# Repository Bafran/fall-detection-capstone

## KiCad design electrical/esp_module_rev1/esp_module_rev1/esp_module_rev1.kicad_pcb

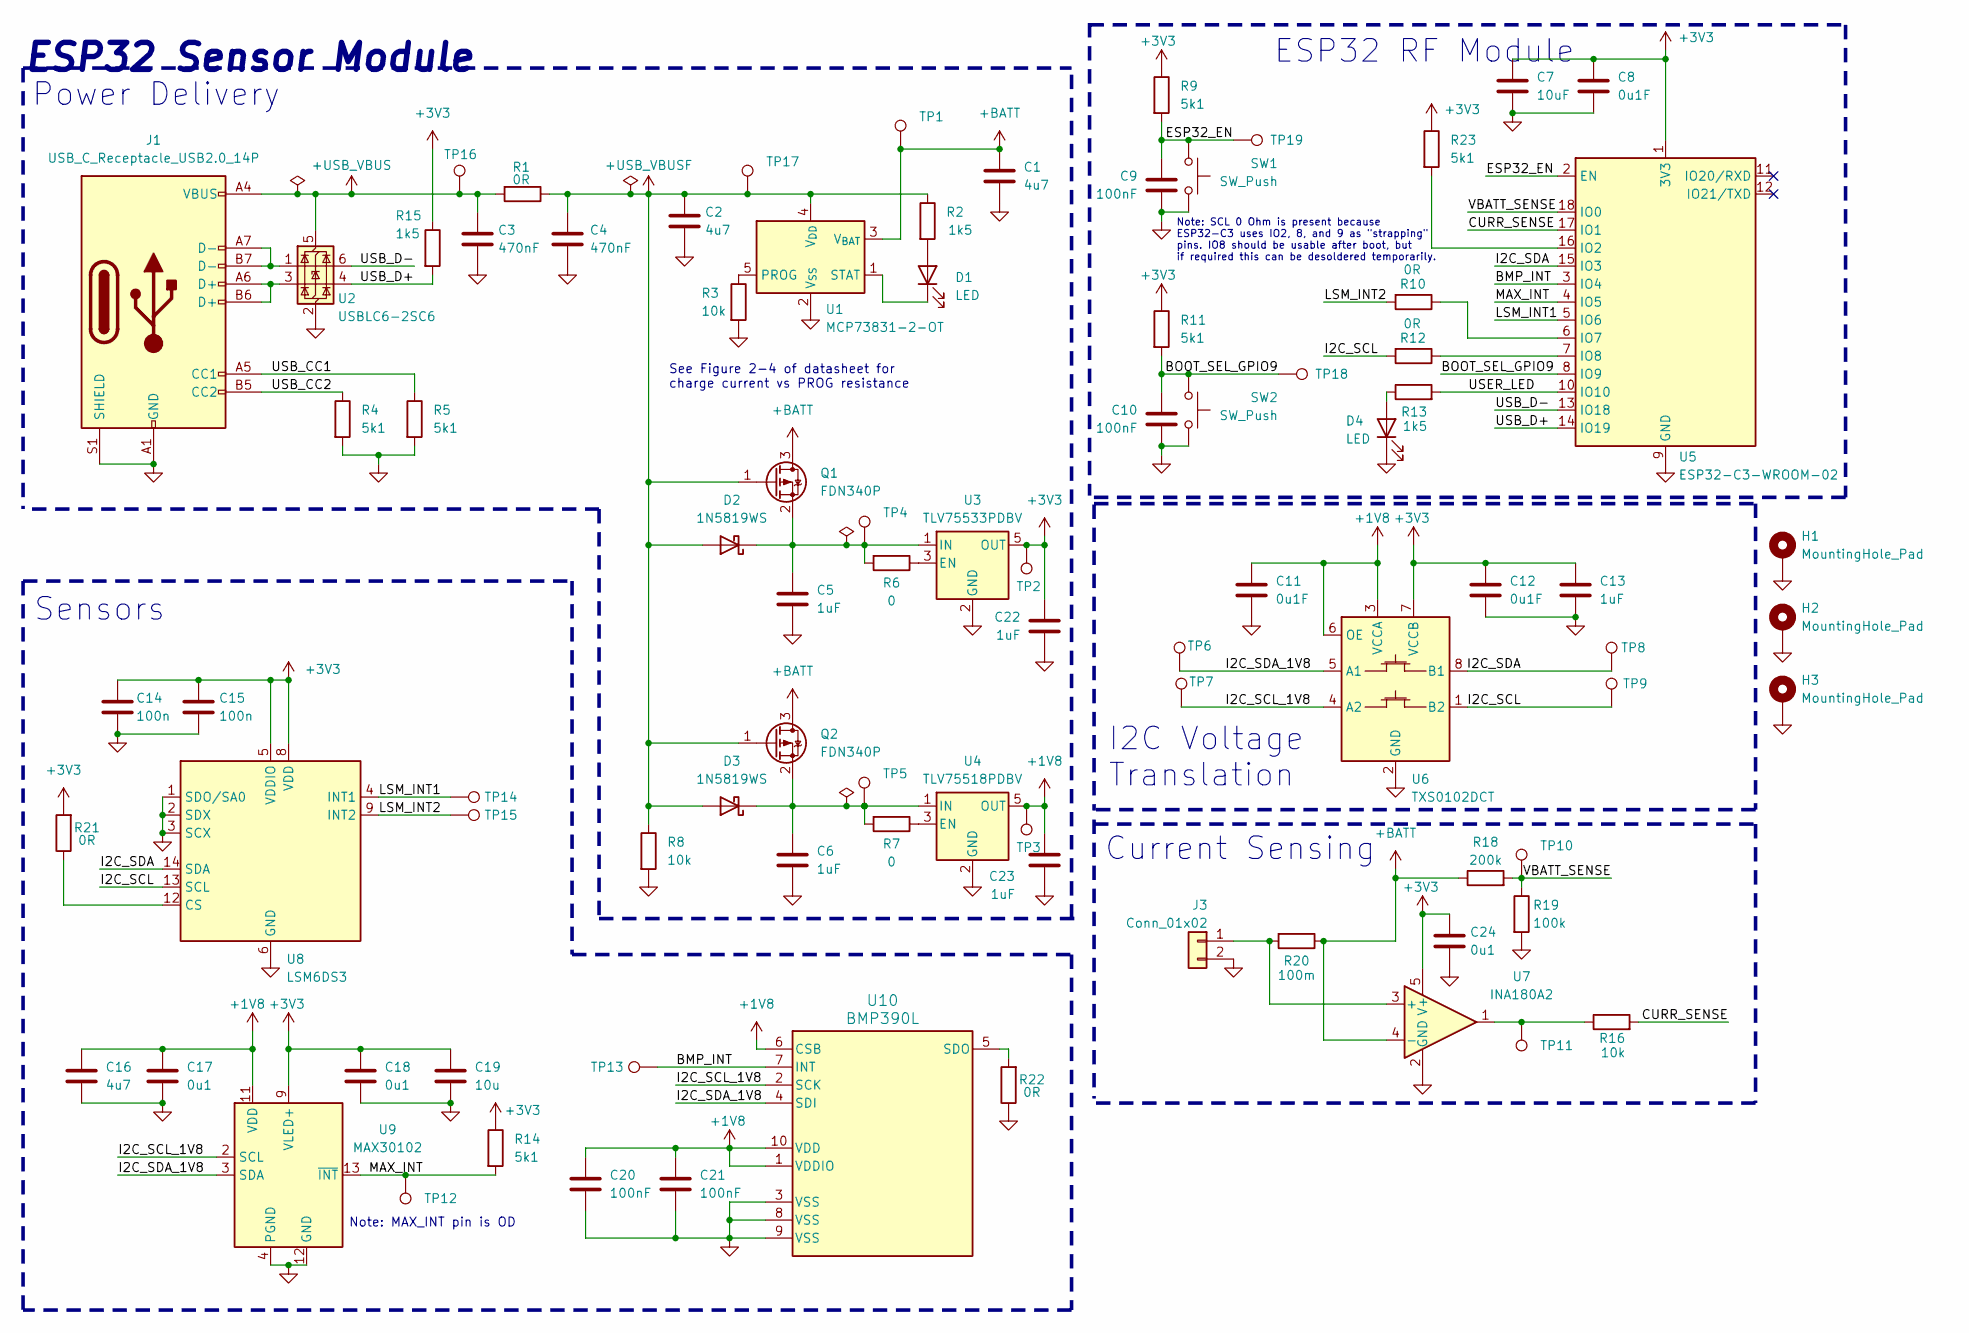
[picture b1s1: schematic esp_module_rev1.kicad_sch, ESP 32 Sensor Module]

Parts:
C1, C2, C16: 4u7; C_0603_1608Metric_Pad1.08x0.95mm_HandSolder
C3, C4: 470nF; C_0603_1608Metric_Pad1.08x0.95mm_HandSolder
C5, C6, C13, C22, C23: 1uF; C_0603_1608Metric_Pad1.08x0.95mm_HandSolder
C7: 10uF; C_0603_1608Metric_Pad1.08x0.95mm_HandSolder
C8, C11, C12: 0u1F; C_0603_1608Metric_Pad1.08x0.95mm_HandSolder
C9, C10, C20, C21: 100nF; C_0603_1608Metric_Pad1.08x0.95mm_HandSolder
C14, C15: 100n; C_0603_1608Metric_Pad1.08x0.95mm_HandSolder
C17, C18, C24: 0u1; C_0603_1608Metric_Pad1.08x0.95mm_HandSolder
C19: 10u; C_0603_1608Metric_Pad1.08x0.95mm_HandSolder
D1: LED; LED_0805_2012Metric_Pad1.15x1.40mm_HandSolder
D2, D3: 1N5819WS; D_SOD-323
D4: LED; LED_1206_3216Metric_Pad1.42x1.75mm_HandSolder
H1, H2, H3: MountingHole_Pad; MountingHole_2.2mm_M2_Pad_Via
J1: USB_C_Receptacle_USB2.0_14P; USB_C_Receptacle_GCT_USB4105-xx-A_16P_TopMnt_Horizontal
J3: Conn_01x02; JST_PH_B2B-PH-K_1x02_P2.00mm_Vertical
Q1, Q2: FDN340P; SOT-23
R1, R10, R12, R21, R22: 0R; R_0603_1608Metric_Pad0.98x0.95mm_HandSolder
R2, R13, R15: 1k5; R_0603_1608Metric_Pad0.98x0.95mm_HandSolder
R3, R8, R16: 10k; R_0603_1608Metric_Pad0.98x0.95mm_HandSolder
R4, R5, R9, R11, R14, R23: 5k1; R_0603_1608Metric_Pad0.98x0.95mm_HandSolder
R6, R7: 0; R_0603_1608Metric_Pad0.98x0.95mm_HandSolder
R18: 200k; R_0603_1608Metric_Pad0.98x0.95mm_HandSolder
R19: 100k; R_0603_1608Metric_Pad0.98x0.95mm_HandSolder
R20: 100m; R_0603_1608Metric_Pad0.98x0.95mm_HandSolder
SW1, SW2: SW_Push; SW_PUSH_6mm
TP1, TP2, TP3, TP4, TP5, TP6, TP7, TP8, TP9, TP10, TP11, TP12, TP13, TP14, TP15, TP16, TP17, TP18, TP19: TestPoint; TestPoint_THTPad_D1.5mm_Drill0.7mm
U1: MCP73831-2-OT; SOT-23-5
U2: USBLC6-2SC6; SOT-23-6
U3: TLV75533PDBV; SOT-23-5
U4: TLV75518PDBV; SOT-23-5
U5: ESP32-C3-WROOM-02
U6: TXS0102DCT; SSOP-8_2.95x2.8mm_P0.65mm
U7: INA180A2; SOT-23-5
U8: LSM6DS3; LGA-14_3x2.5mm_P0.5mm_LayoutBorder3x4y
U9: MAX30102; Maxim_OLGA-14_3.3x5.6mm_P0.8mm
U10: BMP390L; 10LGA_2X2X0p75_BOS

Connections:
+1V8: C11.1, C16.1, C17.1, C20.1, C21.1, C23.1, TP3.1, U4.5 (OUT), U6.3 (VCCA), U6.6 (OE), U9.11 (VDD), U10.1 (VDDIO), U10.6 (CSB), U10.10 (VDD)
+3V3: C7.1, C8.1, C12.1, C13.1, C14.1, C15.1, C18.1, C19.1, C22.1, C24.1, R9.1, R11.1, R14.1, R15.1, R21.2, R23.1, TP2.1, U3.5 (OUT), U5.1 (3V3), U6.7 (VCCB), U7.5 (V+), U8.5 (VDDIO), U8.8 (VDD), U9.9 (VLED+), U9.10 (VLED+)
+BATT: C1.1, Q1.3 (D), Q2.3 (D), R18.1, R20.1, TP1.1, U1.3 (V_{BAT}), U7.4 (-)
+USB_VBUS: C3.1, J1.A4 (VBUS), J1.A9 (VBUS), J1.B4 (VBUS), J1.B9 (VBUS), R1.2, TP16.1, U2.5 (VBUS)
+USB_VBUSF: C2.1, C4.1, D2.2 (A), D3.2 (A), Q1.1 (G), Q2.1 (G), R1.1, R2.1, R8.1, TP17.1, U1.4 (V_{DD})
/BMP_INT: TP13.1, U5.3 (IO4), U10.7 (INT)
/BOOT_SEL_GPIO9: C10.1, R11.2, SW2.2, TP18.1, U5.8 (IO9)
/CURR_SENSE: R16.2, U5.17 (IO1)
/ESP32_EN: C9.1, R9.2, SW1.2, TP19.1, U5.2 (EN)
/I2C_SCL: R12.2, TP9.1, U6.1 (B2), U8.13 (SCL)
/I2C_SCL_1V8: TP7.1, U6.4 (A2), U9.2 (SCL), U10.2 (SCK)
/I2C_SDA: TP8.1, U5.15 (IO3), U6.8 (B1), U8.14 (SDA)
/I2C_SDA_1V8: TP6.1, U6.5 (A1), U9.3 (SDA), U10.4 (SDI)
/LSM_INT1: TP14.1, U5.5 (IO6), U8.4 (INT1)
/LSM_INT2: R10.2, TP15.1, U8.9 (INT2)
/MAX_INT: R14.2, TP12.1, U5.4 (IO5), U9.13 (~INT)
/USB_CC1: J1.A5 (CC1), R5.1
/USB_CC2: J1.B5 (CC2), R4.1
/USB_D+: R15.2, U2.4 (I/O2), U5.14 (IO19)
/USB_D-: U2.6 (I/O1), U5.13 (IO18)
/USER_LED: R13.2, U5.10 (IO10)
/VBATT_SENSE: R18.2, R19.1, TP10.1, U5.18 (IO0)
GND: C1.2, C2.2, C3.2, C4.2, C5.2, C6.2, C7.2, C8.2, C9.2, C10.2, C11.2, C12.2, C13.2, C14.2, C15.2, C16.2, C17.2, C18.2, C19.2, C20.2, C21.2, C22.2, C23.2, C24.2, D4.1 (K), H1.1, H2.1, H3.1, J1.A1 (GND), J1.A12 (GND), J1.B1 (GND), J1.B12 (GND), J1.S1 (SHIELD), J3.2, R3.2, R4.2, R5.2, R8.2, R19.2, R22.1, SW1.1, SW2.1, U1.2 (V_{SS}), U2.2 (GND), U3.2 (GND), U4.2 (GND), U5.9 (GND), U5.19 (GND), U6.2 (GND), U7.2 (GND), U8.1 (SDO/SA0), U8.2 (SDX), U8.3 (SCX), U8.6 (GND), U8.7 (GND), U9.4 (PGND), U9.12 (GND), U10.3 (VSS), U10.8 (VSS), U10.9 (VSS)
unnamed: D1.2 (A), R2.2
unnamed: D1.1 (K), U1.1 (STAT)
unnamed: C5.1, D2.1 (K), Q1.2 (S), R6.2, TP4.1, U3.1 (IN)
unnamed: C6.1, D3.1 (K), Q2.2 (S), R7.2, TP5.1, U4.1 (IN)
unnamed: D4.2 (A), R13.1
unnamed: J1.A6 (D+), J1.B6 (D+), U2.3 (I/O2)
unnamed: J1.A7 (D-), J1.B7 (D-), U2.1 (I/O1)
unnamed: J3.1, R20.2, U7.3 (+)
unnamed: R16.1, TP11.1, U7.1
unnamed: R3.1, U1.5 (PROG)
unnamed: R6.1, U3.3 (EN)
unnamed: R7.1, U4.3 (EN)
unnamed: R23.2, U5.16 (IO2)
unnamed: R10.1, U5.6 (IO7)
unnamed: R12.1, U5.7 (IO8)
unnamed: R21.1, U8.12 (CS)
unnamed: R22.2, U10.5 (SDO)

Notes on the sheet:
Power Delivery
Sensors
Note: SCL 0 Ohm is present because ESP32-C3 uses IO2, 8, and 9 as "strapping" pins. IO8 should be usable after boot, but if required this can be desoldered temporarily.
Note: MAX_INT pin is OD
See Figure 2-4 of datasheet for charge current vs PROG resistance
I2C Voltage Translation
ESP32 RF Module
ESP32 Sensor Module
Current Sensing

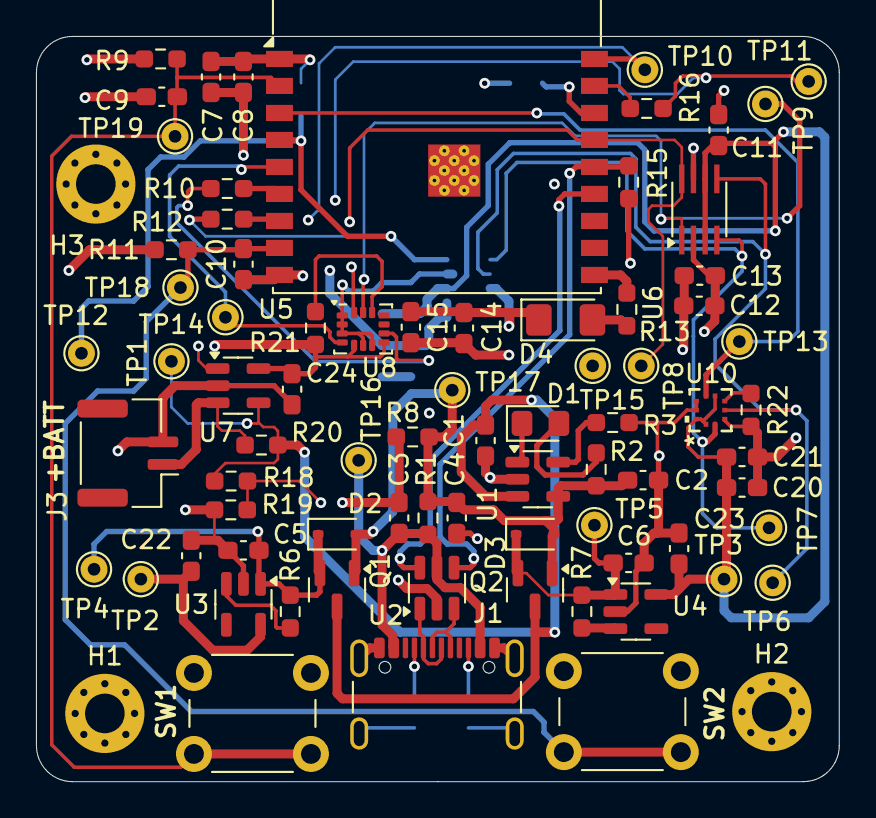
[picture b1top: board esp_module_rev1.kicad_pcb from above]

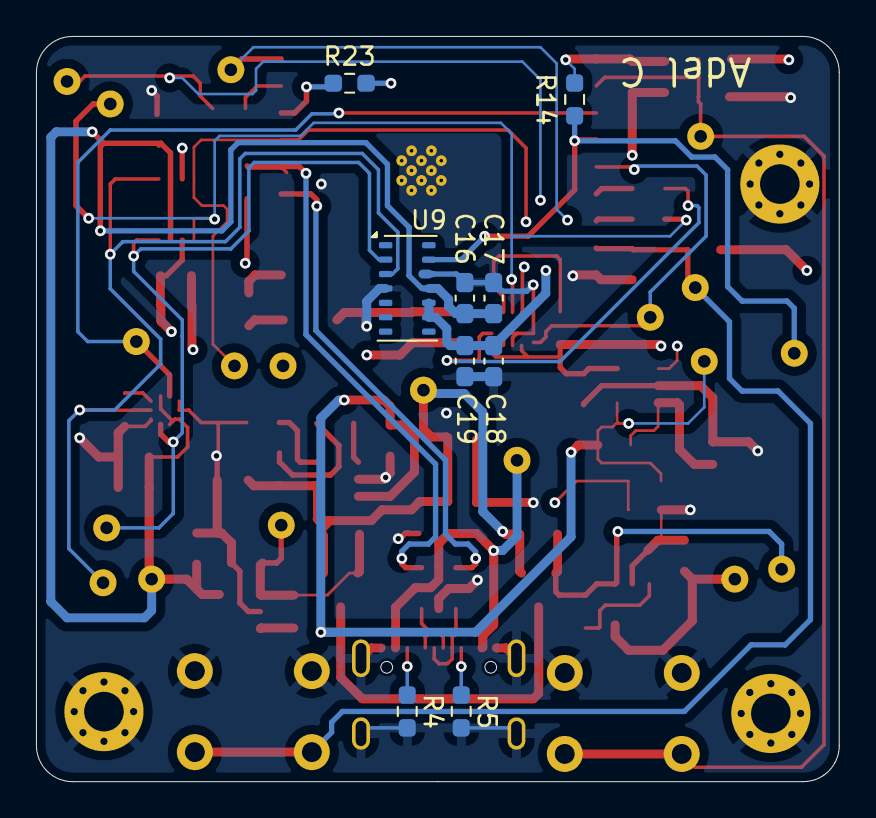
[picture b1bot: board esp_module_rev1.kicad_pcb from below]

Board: 4 copper layers, 44.6 x 41.4 mm, 88 parts (9 on the bottom side), 40 nets.

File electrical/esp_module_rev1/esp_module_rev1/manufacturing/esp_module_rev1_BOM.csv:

Reference,Qty,Value,Footprint,Datasheet
"C1,C2,C16",3,4u7,Capacitor_SMD:C_0603_1608Metric_Pad1.08x0.95mm_HandSolder,~
"C3,C4",2,470nF,Capacitor_SMD:C_0603_1608Metric_Pad1.08x0.95mm_HandSolder,~
"C5,C6,C13,C22,C23",5,1uF,Capacitor_SMD:C_0603_1608Metric_Pad1.08x0.95mm_HandSolder,~
C7,1,10uF,Capacitor_SMD:C_0603_1608Metric_Pad1.08x0.95mm_HandSolder,~
"C8,C11,C12",3,0u1F,Capacitor_SMD:C_0603_1608Metric_Pad1.08x0.95mm_HandSolder,~
"C9,C10,C20,C21",4,100nF,Capacitor_SMD:C_0603_1608Metric_Pad1.08x0.95mm_HandSolder,~
"C14,C15",2,100n,Capacitor_SMD:C_0603_1608Metric_Pad1.08x0.95mm_HandSolder,~
"C17,C18,C24",3,0u1,Capacitor_SMD:C_0603_1608Metric_Pad1.08x0.95mm_HandSolder,~
C19,1,10u,Capacitor_SMD:C_0603_1608Metric_Pad1.08x0.95mm_HandSolder,~
D1,1,LED,LED_SMD:LED_0805_2012Metric_Pad1.15x1.40mm_HandSolder,~
"D2,D3",2,1N5819WS,Diode_SMD:D_SOD-323,https://datasheet.lcsc.com/lcsc/2204281430_Guangdong-Hottech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
D4,1,LED,LED_SMD:LED_1206_3216Metric_Pad1.42x1.75mm_HandSolder,~
J1,1,USB_C_Receptacle_USB2.0_14P,Connector_USB:USB_C_Receptacle_GCT_USB4105-xx-A_16P_TopMnt_Horizontal,https://www.usb.org/sites/default/files/documents/usb_type-c.zip
J3,1,Conn_01x02,Connector_JST:JST_GH_BM02B-GHS-TBT_1x02-1MP_P1.25mm_Vertical,~
"Q1,Q2",2,FDN340P,Package_TO_SOT_SMD:SOT-23,https://www.onsemi.com/pub/Collateral/FDN340P-D.PDF
"R1,R10,R12,R21,R22",5,0R,Resistor_SMD:R_0603_1608Metric_Pad0.98x0.95mm_HandSolder,~
"R2,R13,R15",3,1k5,Resistor_SMD:R_0603_1608Metric_Pad0.98x0.95mm_HandSolder,~
"R3,R8,R16",3,10k,Resistor_SMD:R_0603_1608Metric_Pad0.98x0.95mm_HandSolder,~
"R4,R5,R9,R11,R14,R23",6,5k1,Resistor_SMD:R_0603_1608Metric_Pad0.98x0.95mm_HandSolder,~
"R6,R7",2,0,Resistor_SMD:R_0603_1608Metric_Pad0.98x0.95mm_HandSolder,~
R18,1,200k,Resistor_SMD:R_0603_1608Metric_Pad0.98x0.95mm_HandSolder,~
R19,1,100k,Resistor_SMD:R_0603_1608Metric_Pad0.98x0.95mm_HandSolder,~
R20,1,100m,Resistor_SMD:R_0603_1608Metric_Pad0.98x0.95mm_HandSolder,~
"SW1,SW2",2,SW_Push,Button_Switch_THT:SW_PUSH_6mm,~
"TP1,TP2,TP3,TP4,TP5,TP6,TP7,TP8,TP9,TP10,TP11,TP12,TP13,TP14,TP15,TP16,TP17,TP18,TP19",19,TestPoint,TestPoint:TestPoint_THTPad_D1.5mm_Drill0.7mm,~
U1,1,MCP73831-2-OT,Package_TO_SOT_SMD:SOT-23-5,http://ww1.microchip.com/downloads/en/DeviceDoc/20001984g.pdf
U2,1,USBLC6-2SC6,Package_TO_SOT_SMD:SOT-23-6,https://www.st.com/resource/en/datasheet/usblc6-2.pdf
U3,1,TLV75533PDBV,Package_TO_SOT_SMD:SOT-23-5,http://www.ti.com/lit/ds/symlink/tlv755p.pdf
U4,1,TLV75518PDBV,Package_TO_SOT_SMD:SOT-23-5,http://www.ti.com/lit/ds/symlink/tlv755p.pdf
U5,1,ESP32-C3-WROOM-02,RF_Module:ESP32-C3-WROOM-02,https://www.espressif.com/sites/default/files/documentation/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
U6,1,TXS0102DCT,Package_SO:SSOP-8_2.95x2.8mm_P0.65mm,http://www.ti.com/lit/gpn/txs0102
U7,1,INA180A2,Package_TO_SOT_SMD:SOT-23-5,http://www.ti.com/lit/ds/symlink/ina180.pdf
U8,1,LSM6DS3,Package_LGA:LGA-14_3x2.5mm_P0.5mm_LayoutBorder3x4y,https://www.st.com/resource/en/datasheet/lsm6ds3tr-c.pdf
U9,1,MAX30102,OptoDevice:Maxim_OLGA-14_3.3x5.6mm_P0.8mm,https://datasheets.maximintegrated.com/en/ds/MAX30102.pdf

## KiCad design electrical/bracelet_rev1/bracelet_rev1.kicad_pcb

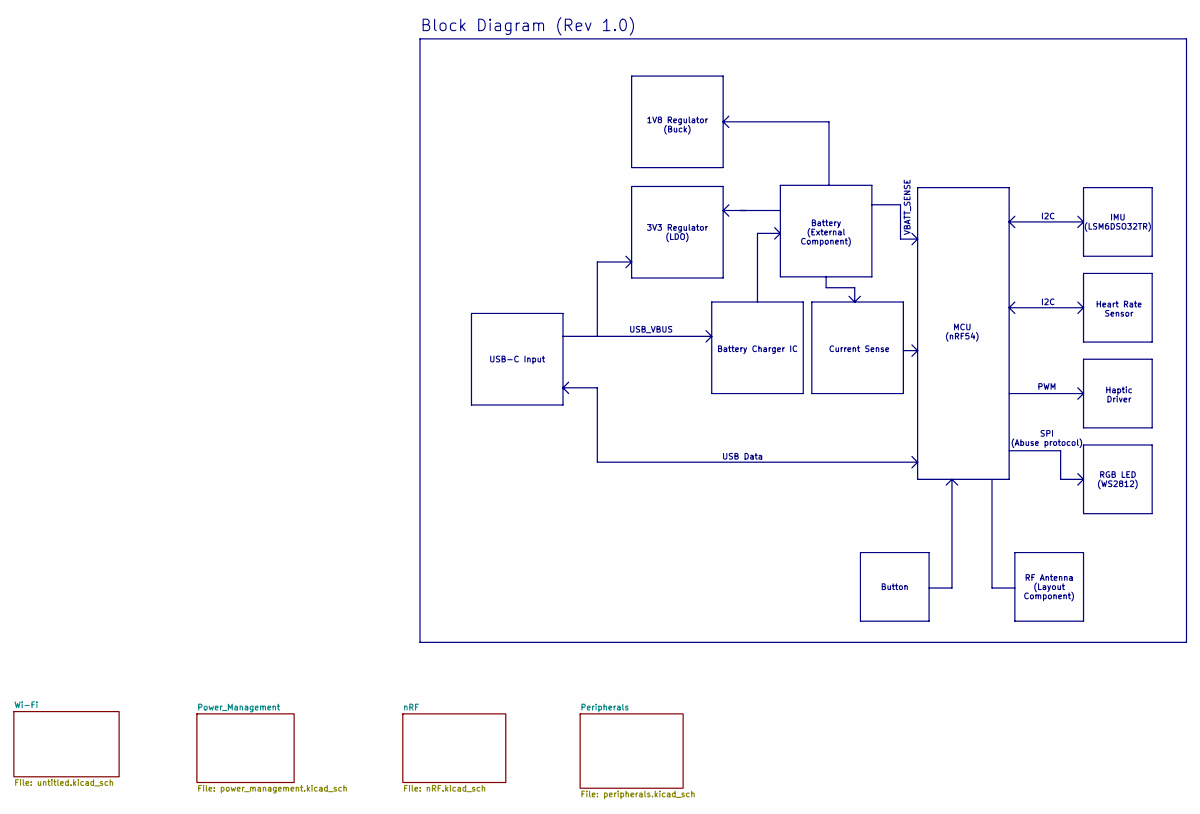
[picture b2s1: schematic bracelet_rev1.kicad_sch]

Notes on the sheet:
VBATT_SENSE
I2C
3V3 Regulator (LDO)
Haptic Driver
RGB LED (WS2812)
USB Data
Current Sense
IMU (LSM6DSO32TR)
SPI (Abuse protocol)
MCU (nRF54)
USB_VBUS
1V8 Regulator (Buck)
RF Antenna (Layout Component)
Block Diagram (Rev 1.0)
Button
Battery (External Component)
PWM
Battery Charger IC
Heart Rate Sensor
USB-C Input

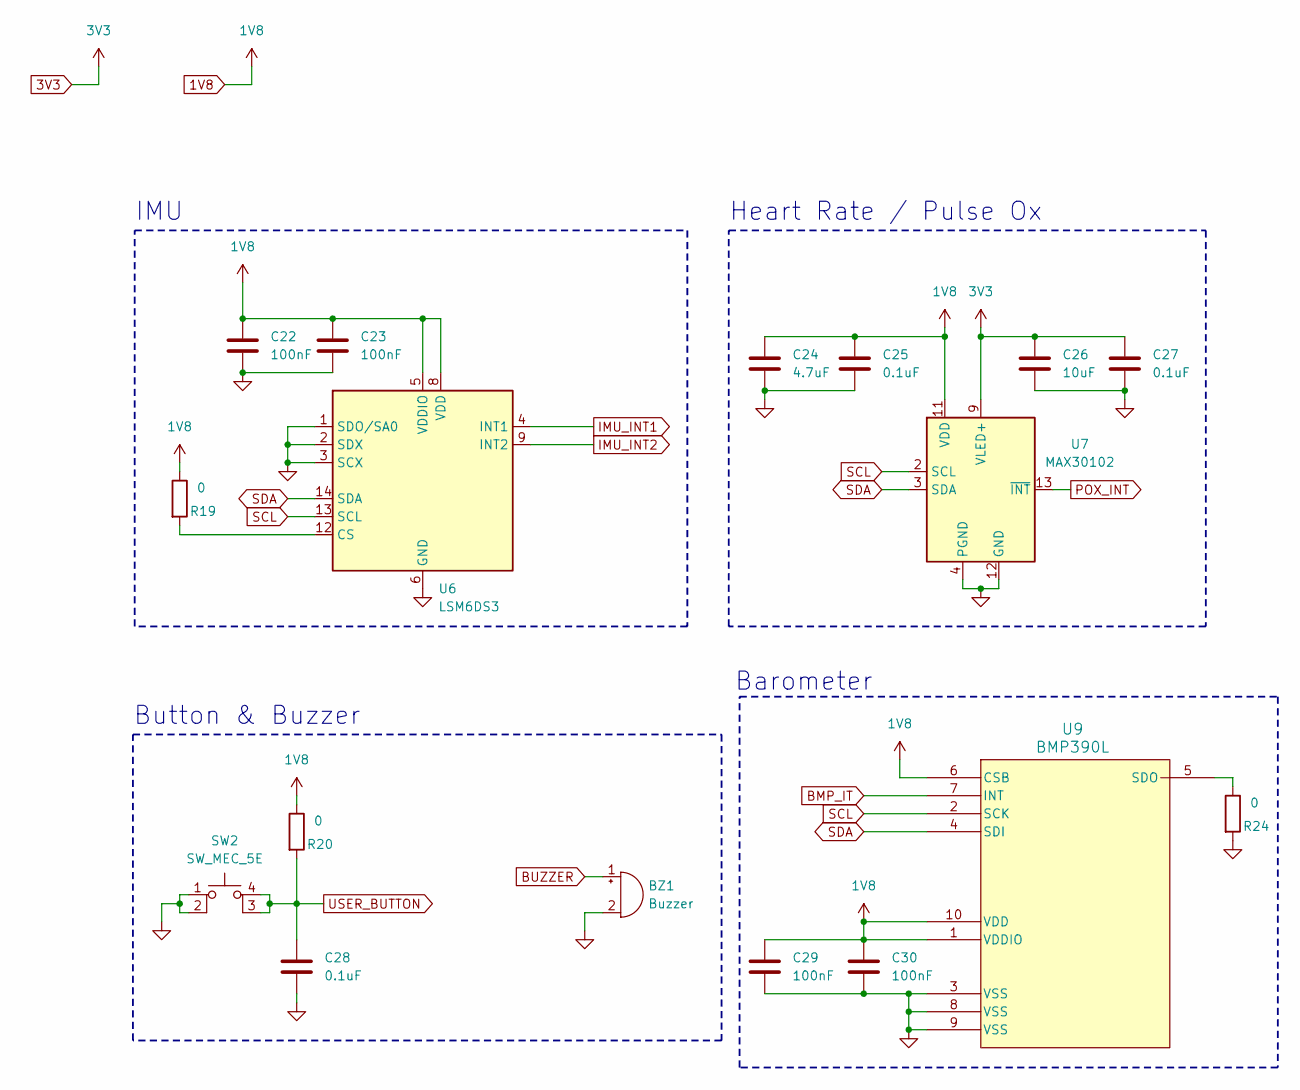
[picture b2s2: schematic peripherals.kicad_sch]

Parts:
BZ1: Buzzer
C22, C23, C29, C30: 100nF; C_0603_1608Metric_Pad1.08x0.95mm_HandSolder
C24: 4.7uF; C_0603_1608Metric_Pad1.08x0.95mm_HandSolder
C25, C27, C28: 0.1uF; C_0603_1608Metric_Pad1.08x0.95mm_HandSolder
C26: 10uF; C_0603_1608Metric_Pad1.08x0.95mm_HandSolder
R19, R20: 0; R_0603_1608Metric_Pad0.98x0.95mm_HandSolder
R24: 0; R_0201_0603Metric_Pad0.64x0.40mm_HandSolder
SW2: SW_MEC_5E; SW_MEC_5GSH9
U6: LSM6DS3; LGA-14_3x2.5mm_P0.5mm_LayoutBorder3x4y
U7: MAX30102; Maxim_OLGA-14_3.3x5.6mm_P0.8mm
U9: BMP390L

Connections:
3V3: C26.1, C27.1, U7.9 (VLED+), U7.10 (VLED+); also elsewhere on the board
GND: BZ1.2 (-), C22.2, C23.2, C24.2, C25.2, C26.2, C27.2, C28.2, C29.2, C30.2, R24.2, SW2.1, SW2.2, U6.1 (SDO/SA0), U6.2 (SDX), U6.3 (SCX), U6.6 (GND), U6.7 (GND), U7.4 (PGND), U7.12 (GND), U9.3 (VSS), U9.8 (VSS), U9.9 (VSS); also elsewhere on the board
IMU_INT1: U6.4 (INT1); also elsewhere on the board
IMU_INT2: U6.9 (INT2); also elsewhere on the board
unnamed: R19.2, U6.12 (CS)
unnamed: R24.1, U9.5 (SDO)
POX_INT: U7.13 (~INT); also elsewhere on the board
SCL: U6.13 (SCL), U7.2 (SCL), U9.2 (SCK); also elsewhere on the board
SDA: U6.14 (SDA), U7.3 (SDA), U9.4 (SDI); also elsewhere on the board
USER_BUTTON: C28.1, R20.2, SW2.3 (K), SW2.4 (A); also elsewhere on the board

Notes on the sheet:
Button & Buzzer
Heart Rate / Pulse Ox
IMU
Barometer

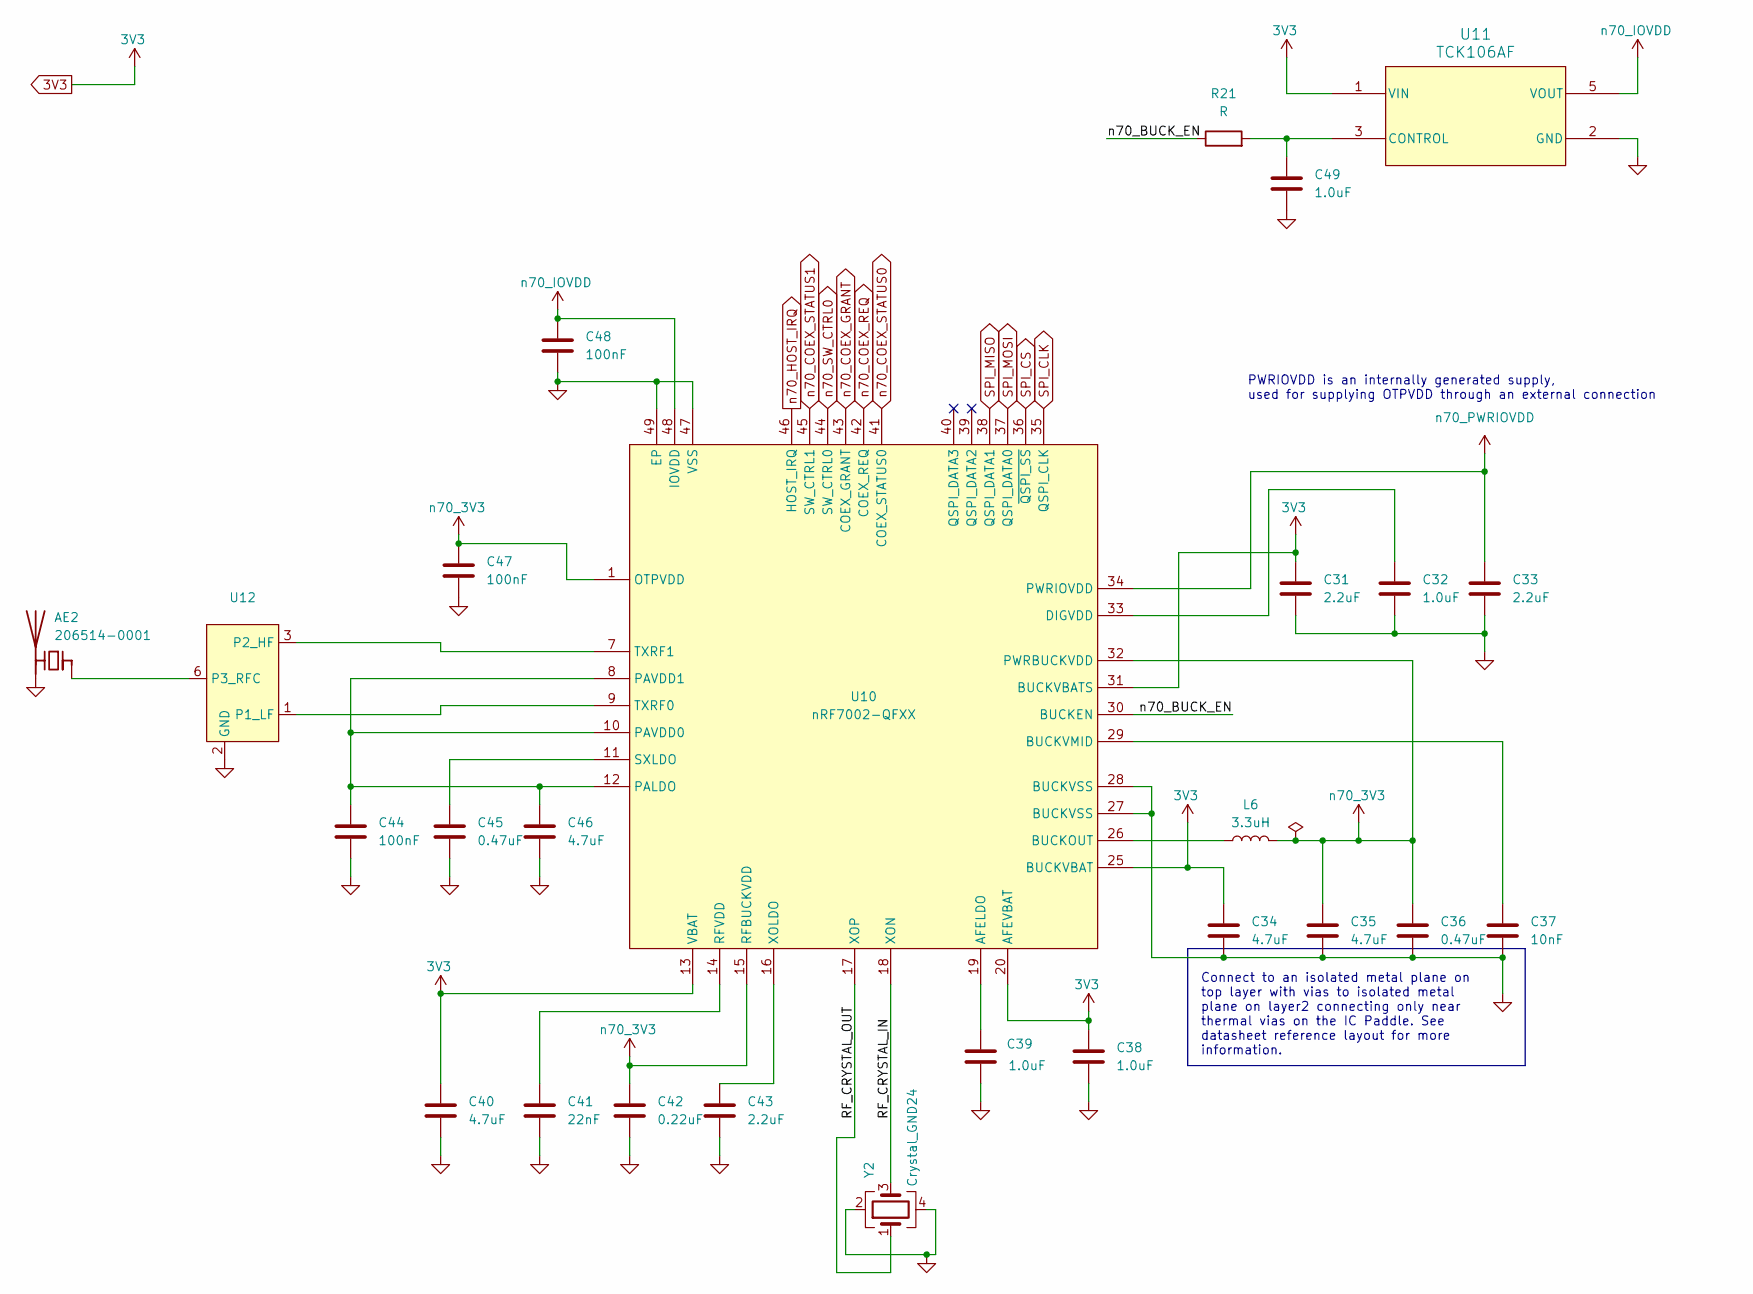
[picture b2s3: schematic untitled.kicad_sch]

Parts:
AE2: 206514-0001
C31, C33, C43: 2.2uF; C_0603_1608Metric_Pad1.08x0.95mm_HandSolder
C32, C38, C39, C49: 1.0uF; C_0603_1608Metric_Pad1.08x0.95mm_HandSolder
C34, C35, C40, C46: 4.7uF; C_0603_1608Metric_Pad1.08x0.95mm_HandSolder
C36, C45: 0.47uF; C_0603_1608Metric_Pad1.08x0.95mm_HandSolder
C37: 10nF; C_0603_1608Metric_Pad1.08x0.95mm_HandSolder
C41: 22nF; C_0603_1608Metric_Pad1.08x0.95mm_HandSolder
C42: 0.22uF; C_0603_1608Metric_Pad1.08x0.95mm_HandSolder
C44, C47, C48: 100nF; C_0603_1608Metric_Pad1.08x0.95mm_HandSolder
L6: 3.3uH; L_0603_1608Metric_Pad1.05x0.95mm_HandSolder
R21: R; R_0201_0603Metric_Pad0.64x0.40mm_HandSolder
U10: nRF7002-QFXX; QFN-48-1EP_6x6mm_P0.4mm_EP4.6x4.6mm_ThermalVias
U11: TCK106AF
U12: (no value)
Y2: Crystal_GND24; Crystal_SMD_3225-4Pin_3.2x2.5mm_HandSoldering

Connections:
3V3: C31.1, C34.1, C38.1, C40.1, U10.13 (VBAT), U10.20 (AFEVBAT), U10.25 (BUCKVBAT), U10.31 (BUCKVBATS), U11.1 (VIN); also elsewhere on the board
/Wi-Fi/RF_CRYSTAL_IN: U10.18 (XON), Y2.3
/Wi-Fi/RF_CRYSTAL_OUT: U10.17 (XOP), Y2.1
/Wi-Fi/n70_BUCK_EN: R21.1, U10.30 (BUCKEN)
GND: AE2.2 (PCB_Trace), C31.2, C32.2, C33.2, C34.2, C35.2, C36.2, C37.2, C38.2, C39.2, C40.2, C41.2, C42.2, C43.2, C44.2, C45.2, C46.2, C47.2, C48.2, C49.2, U10.27 (BUCKVSS), U10.28 (BUCKVSS), U10.47 (VSS), U10.49 (EP), U11.2 (GND), U12.2 (GND), U12.5 (GND), U12.7 (GND), Y2.2, Y2.4; also elsewhere on the board
unnamed: AE2.1 (FEED), U12.6 (P3_RFC)
unnamed: C39.1, U10.19 (AFELDO)
unnamed: L6.1, U10.26 (BUCKOUT)
unnamed: C37.1, U10.29 (BUCKVMID)
unnamed: C32.1, U10.33 (DIGVDD)
unnamed: C44.1, C46.1, U10.8 (PAVDD1), U10.10 (PAVDD0), U10.12 (PALDO)
unnamed: C41.1, U10.14 (RFVDD)
unnamed: C45.1, U10.11 (SXLDO)
unnamed: U10.9 (TXRF0), U12.1 (P1_LF)
unnamed: U10.7 (TXRF1), U12.3 (P2_HF)
unnamed: C43.1, U10.16 (XOLDO)
unnamed: C49.1, R21.2, U11.3 (CONTROL)
SPI_CLK: U10.35 (QSPI_CLK); also elsewhere on the board
SPI_CS: U10.36 (~QSPI_SS); also elsewhere on the board
SPI_MISO: U10.38 (QSPI_DATA1); also elsewhere on the board
SPI_MOSI: U10.37 (QSPI_DATA0); also elsewhere on the board
n70_3V3: C35.1, C36.1, C42.1, C47.1, L6.2, U10.1 (OTPVDD), U10.15 (RFBUCKVDD), U10.32 (PWRBUCKVDD)
n70_COEX_GRANT: U10.43 (COEX_GRANT); also elsewhere on the board
n70_COEX_REQ: U10.42 (COEX_REQ); also elsewhere on the board
n70_COEX_STATUS0: U10.41 (COEX_STATUS0); also elsewhere on the board
n70_COEX_STATUS1: U10.45 (SW_CTRL1); also elsewhere on the board
n70_HOST_IRQ: U10.46 (HOST_IRQ); also elsewhere on the board
n70_IOVDD: C48.1, U10.48 (IOVDD), U11.5 (VOUT)
n70_PWRIOVDD: C33.1, U10.34 (PWRIOVDD)
n70_SW_CTRL0: U10.44 (SW_CTRL0); also elsewhere on the board

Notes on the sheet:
PWRIOVDD is an internally generated supply, used for supplying OTPVDD through an external connection
Connect to an isolated metal plane on top layer with vias to isolated metal plane on layer2 connecting only near thermal vias on the IC Paddle. See datasheet reference layout for more information.

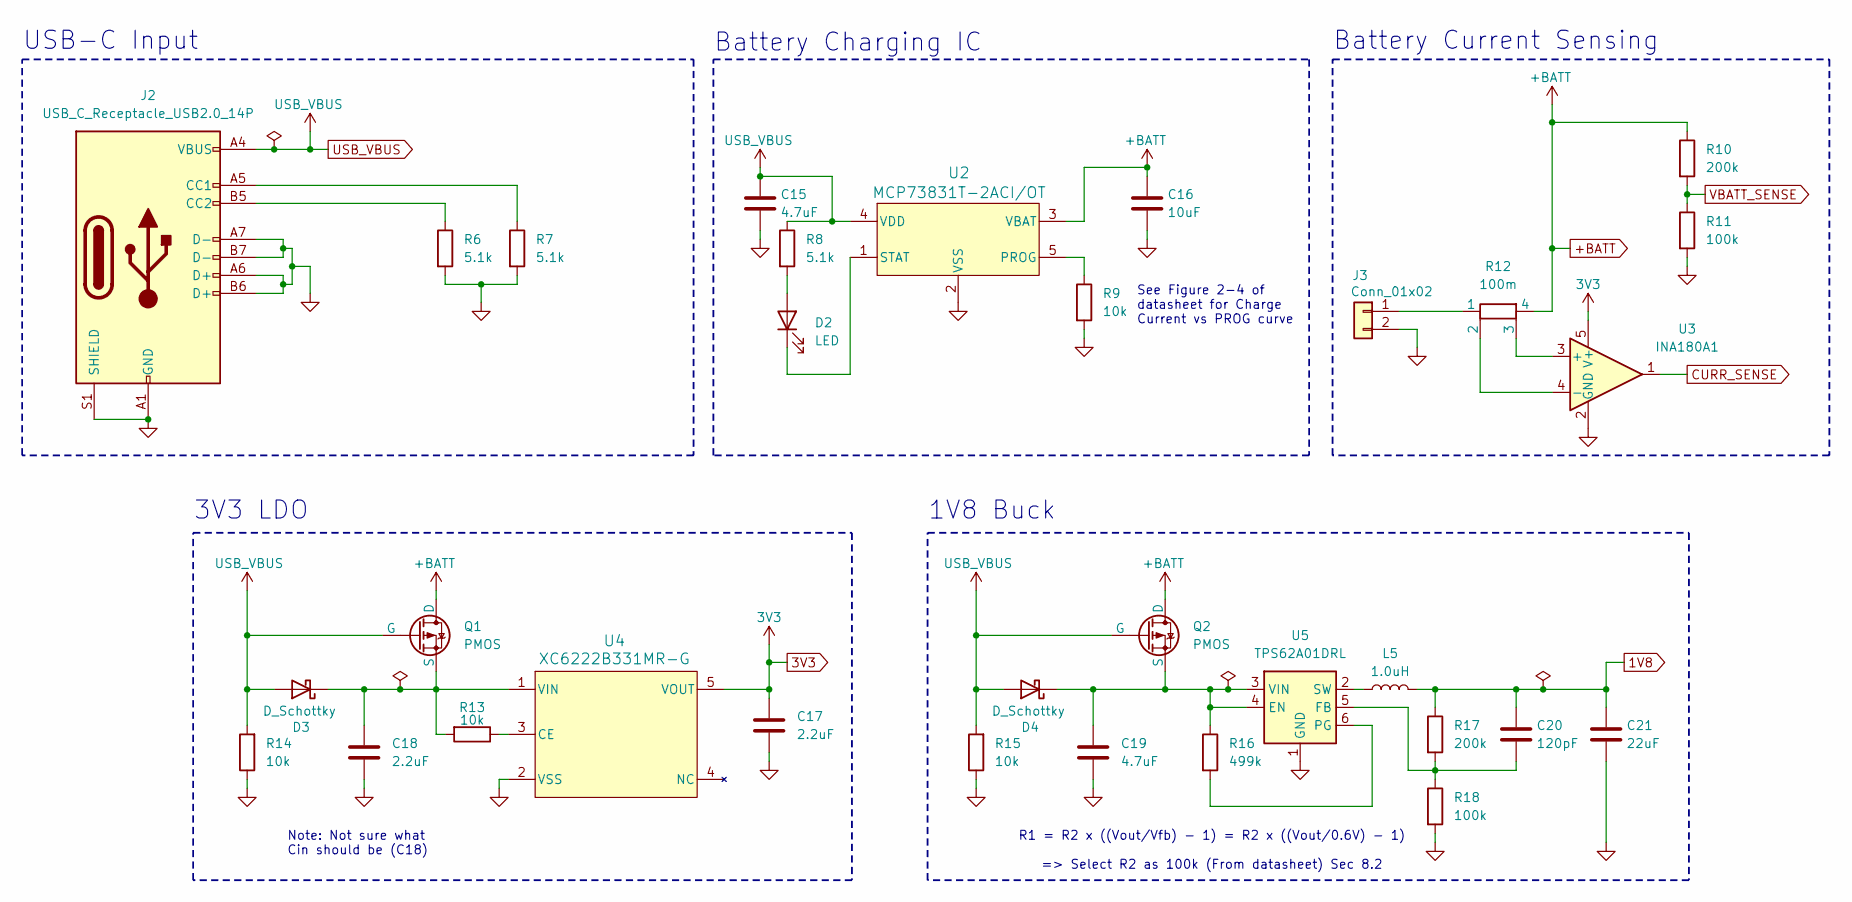
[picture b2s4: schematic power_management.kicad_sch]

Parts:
C15, C19: 4.7uF; C_0603_1608Metric_Pad1.08x0.95mm_HandSolder
C16: 10uF; C_0603_1608Metric_Pad1.08x0.95mm_HandSolder
C17, C18: 2.2uF; C_0603_1608Metric_Pad1.08x0.95mm_HandSolder
C20: 120pF; C_0603_1608Metric_Pad1.08x0.95mm_HandSolder
C21: 22uF; C_0603_1608Metric_Pad1.08x0.95mm_HandSolder
D2: LED; LED_0603_1608Metric_Pad1.05x0.95mm_HandSolder
D3, D4: D_Schottky; D_0603_1608Metric_Pad1.05x0.95mm_HandSolder
J2: USB_C_Receptacle_USB2.0_14P
J3: Conn_01x02; JST_PH_B2B-PH-K_1x02_P2.00mm_Vertical
L5: 1.0uH; L_0603_1608Metric_Pad1.05x0.95mm_HandSolder
Q1, Q2: PMOS; SOT-23-3
R6, R7, R8: 5.1k; R_0603_1608Metric_Pad0.98x0.95mm_HandSolder
R9, R13, R14, R15: 10k; R_0603_1608Metric_Pad0.98x0.95mm_HandSolder
R10, R17: 200k; R_0603_1608Metric_Pad0.98x0.95mm_HandSolder
R11, R18: 100k; R_0603_1608Metric_Pad0.98x0.95mm_HandSolder
R12: 100m; R_Shunt_Ohmite_LVK12
R16: 499k; R_0603_1608Metric_Pad0.98x0.95mm_HandSolder
U2: MCP73831T-2ACI/OT
U3: INA180A1; SOT-23-5
U4: XC6222B331MR-G
U5: TPS62A01DRL; SOT-563

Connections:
3V3: C17.1, U2.6 (V_{CCB}), U3.5 (V+), U4.5 (VOUT); also elsewhere on the board
CURR_SENSE: U3.1; also elsewhere on the board
GND: C15.2, C16.2, C17.2, C18.2, C19.2, C21.2, J2.A1 (GND), J2.A6 (D+), J2.A7 (D-), J2.A12 (GND), J2.B1 (GND), J2.B6 (D+), J2.B7 (D-), J2.B12 (GND), J2.S1 (SHIELD), J3.2, R6.2, R7.2, R9.2, R11.2, R14.1, R15.1, R18.2, U2.2 (GND), U3.2 (GND), U4.2 (VSS), U5.1 (GND); also elsewhere on the board
unnamed: D2.2 (A), R8.2
unnamed: C18.1, D3.1 (K), Q1.3 (S), R13.2, U4.1 (VIN)
unnamed: C19.1, D4.1 (K), Q2.3 (S), R16.1, U5.3 (VIN), U5.4 (EN)
unnamed: J2.A5 (CC1), R7.1
unnamed: J2.B5 (CC2), R6.1
unnamed: J3.1, R12.1
unnamed: R12.3, U3.3 (+)
unnamed: R12.2, U3.4 (-)
unnamed: R13.1, U4.3 (CE)
unnamed: C20.2, R17.2, R18.1, U5.5 (FB)
unnamed: R16.2, U5.6 (PG)
unnamed: L5.1, U5.2 (SW)
VBATT_SENSE: R10.2, R11.1; also elsewhere on the board

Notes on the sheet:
R1 = R2 x ((Vout/Vfb) - 1) = R2 x ((Vout/0.6V) - 1) => Select R2 as 100k (From datasheet) Sec 8.2
Note: Not sure what Cin should be (C18)
See Figure 2-4 of datasheet for Charge Current vs PROG curve
3V3 LDO
1V8 Buck
Battery Current Sensing
USB-C Input
Battery Charging IC
